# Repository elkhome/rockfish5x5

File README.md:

# rockfish5x5
5x5 expandable mechanical keyboard, powered by a Raspberry Pi Pico.

Shared for reference without licence. Not especially original. Feel free to use my design as a reference to design your own board, but I probably wouldn't reccomend trying to build this as is.

Entire design is upside down, and the uploaded revision has not been tested. To acheive the two board layout, the Pico goes on the right board and the solder jumpers are bridged on the left board.

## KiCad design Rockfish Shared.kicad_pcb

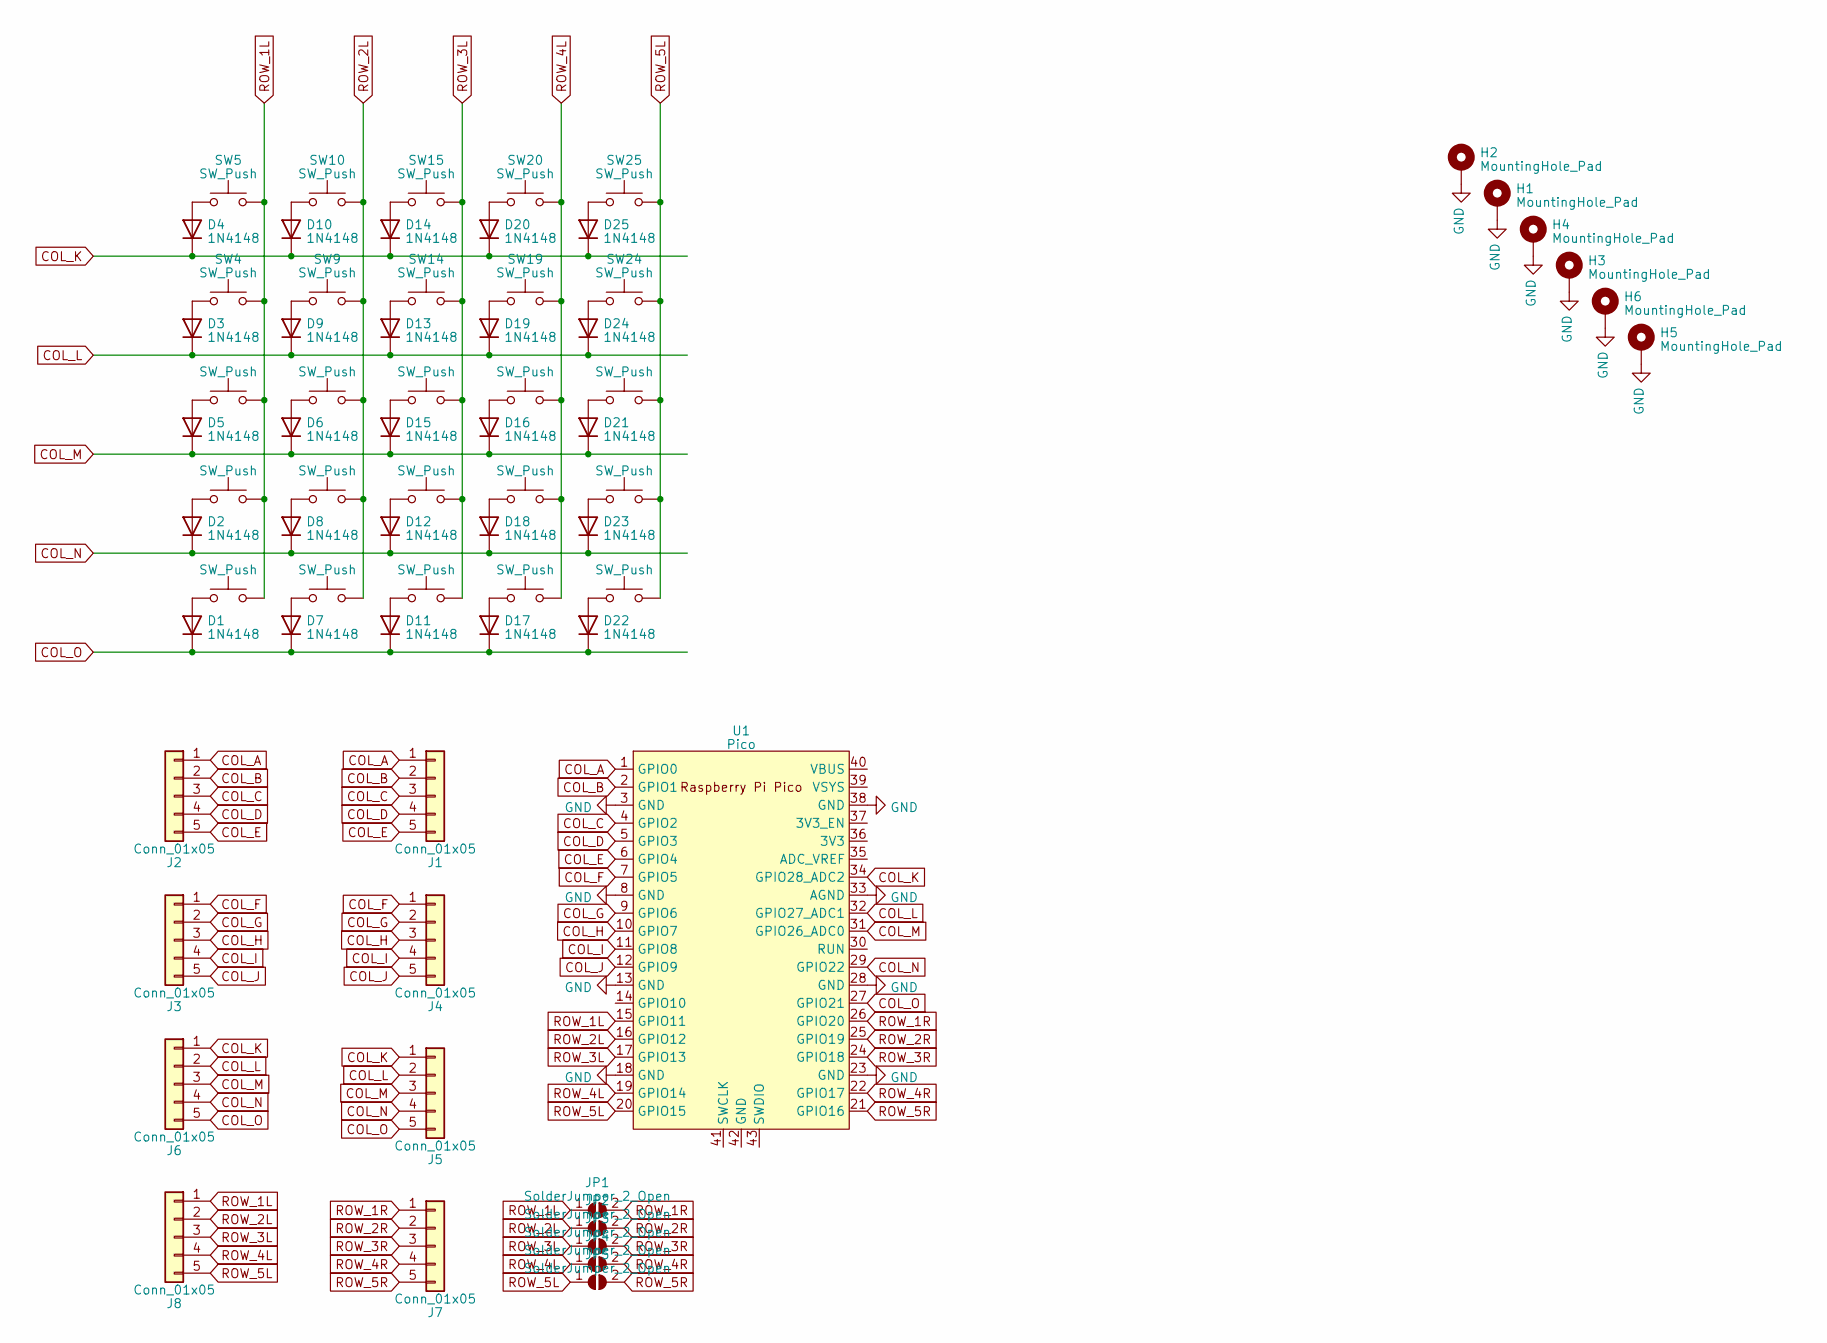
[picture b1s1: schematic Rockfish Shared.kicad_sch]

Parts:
D1, D2, D3, D4, D5, D6, D7, D8, D9, D10, D11, D12, D13, D14, D15, D16, D17, D18, D19, D20, D21, D22, D23, D24, D25: 1N4148; D_DO-35_SOD27_P7.62mm_Horizontal_no_front_silk
H1, H2, H3, H4, H5, H6: MountingHole_Pad; MountingHole_2.2mm_M2_DIN965_Pad
J1, J2, J3, J4, J5, J6, J7, J8: Conn_01x05; PinHeader_1x05_P2.54mm_Vertical
JP1, JP2, JP3, JP4, JP5: SolderJumper_2_Open; SolderJumper-2_P1.3mm_Open_RoundedPad1.0x1.5mm
SW1, SW2, SW3, SW4, SW5, SW6, SW7, SW8, SW9, SW10, SW11, SW12, SW13, SW14, SW15, SW16, SW17, SW18, SW19, SW20, SW21, SW22, SW23, SW24, SW25: SW_Push; SW_MX_reversible_flip_no_back_silk
U1: Pico; RPi_Pico_SMD_TH

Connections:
COL_A: J1.1, J2.1, U1.1 (GPIO0)
COL_B: J1.2, J2.2, U1.2 (GPIO1)
COL_C: J1.3, J2.3, U1.4 (GPIO2)
COL_D: J1.4, J2.4, U1.5 (GPIO3)
COL_E: J1.5, J2.5, U1.6 (GPIO4)
COL_F: J3.1, J4.1, U1.7 (GPIO5)
COL_G: J3.2, J4.2, U1.9 (GPIO6)
COL_H: J3.3, J4.3, U1.10 (GPIO7)
COL_I: J3.4, J4.4, U1.11 (GPIO8)
COL_J: J3.5, J4.5, U1.12 (GPIO9)
COL_K: D4.1 (K), D10.1 (K), D14.1 (K), D20.1 (K), D25.1 (K), J5.1, J6.1, U1.34 (GPIO28_ADC2)
COL_L: D3.1 (K), D9.1 (K), D13.1 (K), D19.1 (K), D24.1 (K), J5.2, J6.2, U1.32 (GPIO27_ADC1)
COL_M: D5.1 (K), D6.1 (K), D15.1 (K), D16.1 (K), D21.1 (K), J5.3, J6.3, U1.31 (GPIO26_ADC0)
COL_N: D2.1 (K), D8.1 (K), D12.1 (K), D18.1 (K), D23.1 (K), J5.4, J6.4, U1.29 (GPIO22)
COL_O: D1.1 (K), D7.1 (K), D11.1 (K), D17.1 (K), D22.1 (K), J5.5, J6.5, U1.27 (GPIO21)
GND: H1.1, H2.1, H3.1, H4.1, H5.1, H6.1, U1.3 (GND), U1.8 (GND), U1.13 (GND), U1.18 (GND), U1.23 (GND), U1.28 (GND), U1.33 (AGND), U1.38 (GND)
unnamed: D4.2 (A), SW5.1
unnamed: D3.2 (A), SW4.1
unnamed: D2.2 (A), SW2.1
unnamed: D1.2 (A), SW1.1
unnamed: D5.2 (A), SW3.1
unnamed: D6.2 (A), SW8.1
unnamed: D10.2 (A), SW10.1
unnamed: D9.2 (A), SW9.1
unnamed: D8.2 (A), SW7.1
unnamed: D7.2 (A), SW6.1
unnamed: D14.2 (A), SW15.1
unnamed: D13.2 (A), SW14.1
unnamed: D12.2 (A), SW12.1
unnamed: D11.2 (A), SW11.1
unnamed: D15.2 (A), SW13.1
unnamed: D16.2 (A), SW18.1
unnamed: D20.2 (A), SW20.1
unnamed: D19.2 (A), SW19.1
unnamed: D18.2 (A), SW17.1
unnamed: D17.2 (A), SW16.1
unnamed: D21.2 (A), SW23.1
unnamed: D25.2 (A), SW25.1
unnamed: D24.2 (A), SW24.1
unnamed: D23.2 (A), SW22.1
unnamed: D22.2 (A), SW21.1
ROW_1L: J8.1, JP1.1 (A), SW1.2, SW2.2, SW3.2, SW4.2, SW5.2, U1.15 (GPIO11)
ROW_1R: J7.1, JP1.2 (B), U1.26 (GPIO20)
ROW_2L: J8.2, JP2.1 (A), SW6.2, SW7.2, SW8.2, SW9.2, SW10.2, U1.16 (GPIO12)
ROW_2R: J7.2, JP2.2 (B), U1.25 (GPIO19)
ROW_3L: J8.3, JP3.1 (A), SW11.2, SW12.2, SW13.2, SW14.2, SW15.2, U1.17 (GPIO13)
ROW_3R: J7.3, JP3.2 (B), U1.24 (GPIO18)
ROW_4L: J8.4, JP4.1 (A), SW16.2, SW17.2, SW18.2, SW19.2, SW20.2, U1.19 (GPIO14)
ROW_4R: J7.4, JP4.2 (B), U1.22 (GPIO17)
ROW_5L: J8.5, JP5.1 (A), SW21.2, SW22.2, SW23.2, SW24.2, SW25.2, U1.20 (GPIO15)
ROW_5R: J7.5, JP5.2 (B), U1.21 (GPIO16)

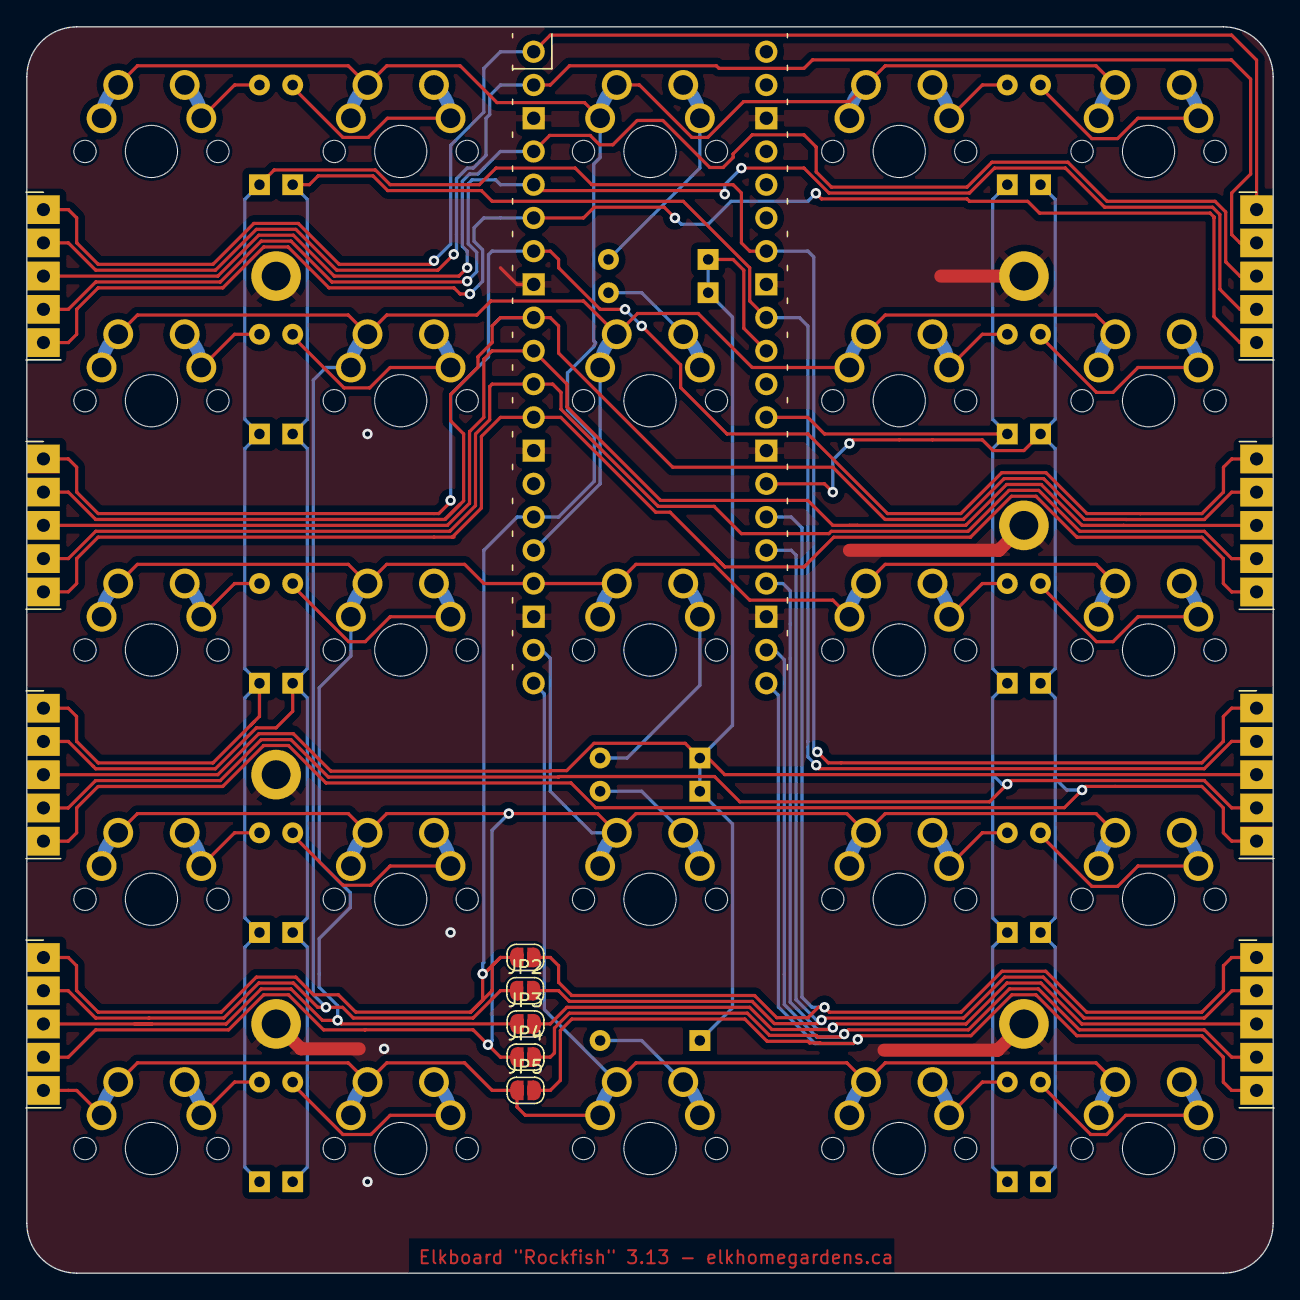
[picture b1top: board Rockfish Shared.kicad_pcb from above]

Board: 2 copper layers, 95.3 x 95.3 mm, 70 parts (0 on the bottom side), 51 nets.

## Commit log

2023-04-18 Uploaded KiCad files.
2023-04-18 Uploaded reference photo.
